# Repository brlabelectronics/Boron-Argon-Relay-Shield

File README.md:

# Boron-Argon-Relay-Shield
Documents and source code for the Boron-Argon Relay Shield.
The Eagle design files can be found in the PCB design files folder.

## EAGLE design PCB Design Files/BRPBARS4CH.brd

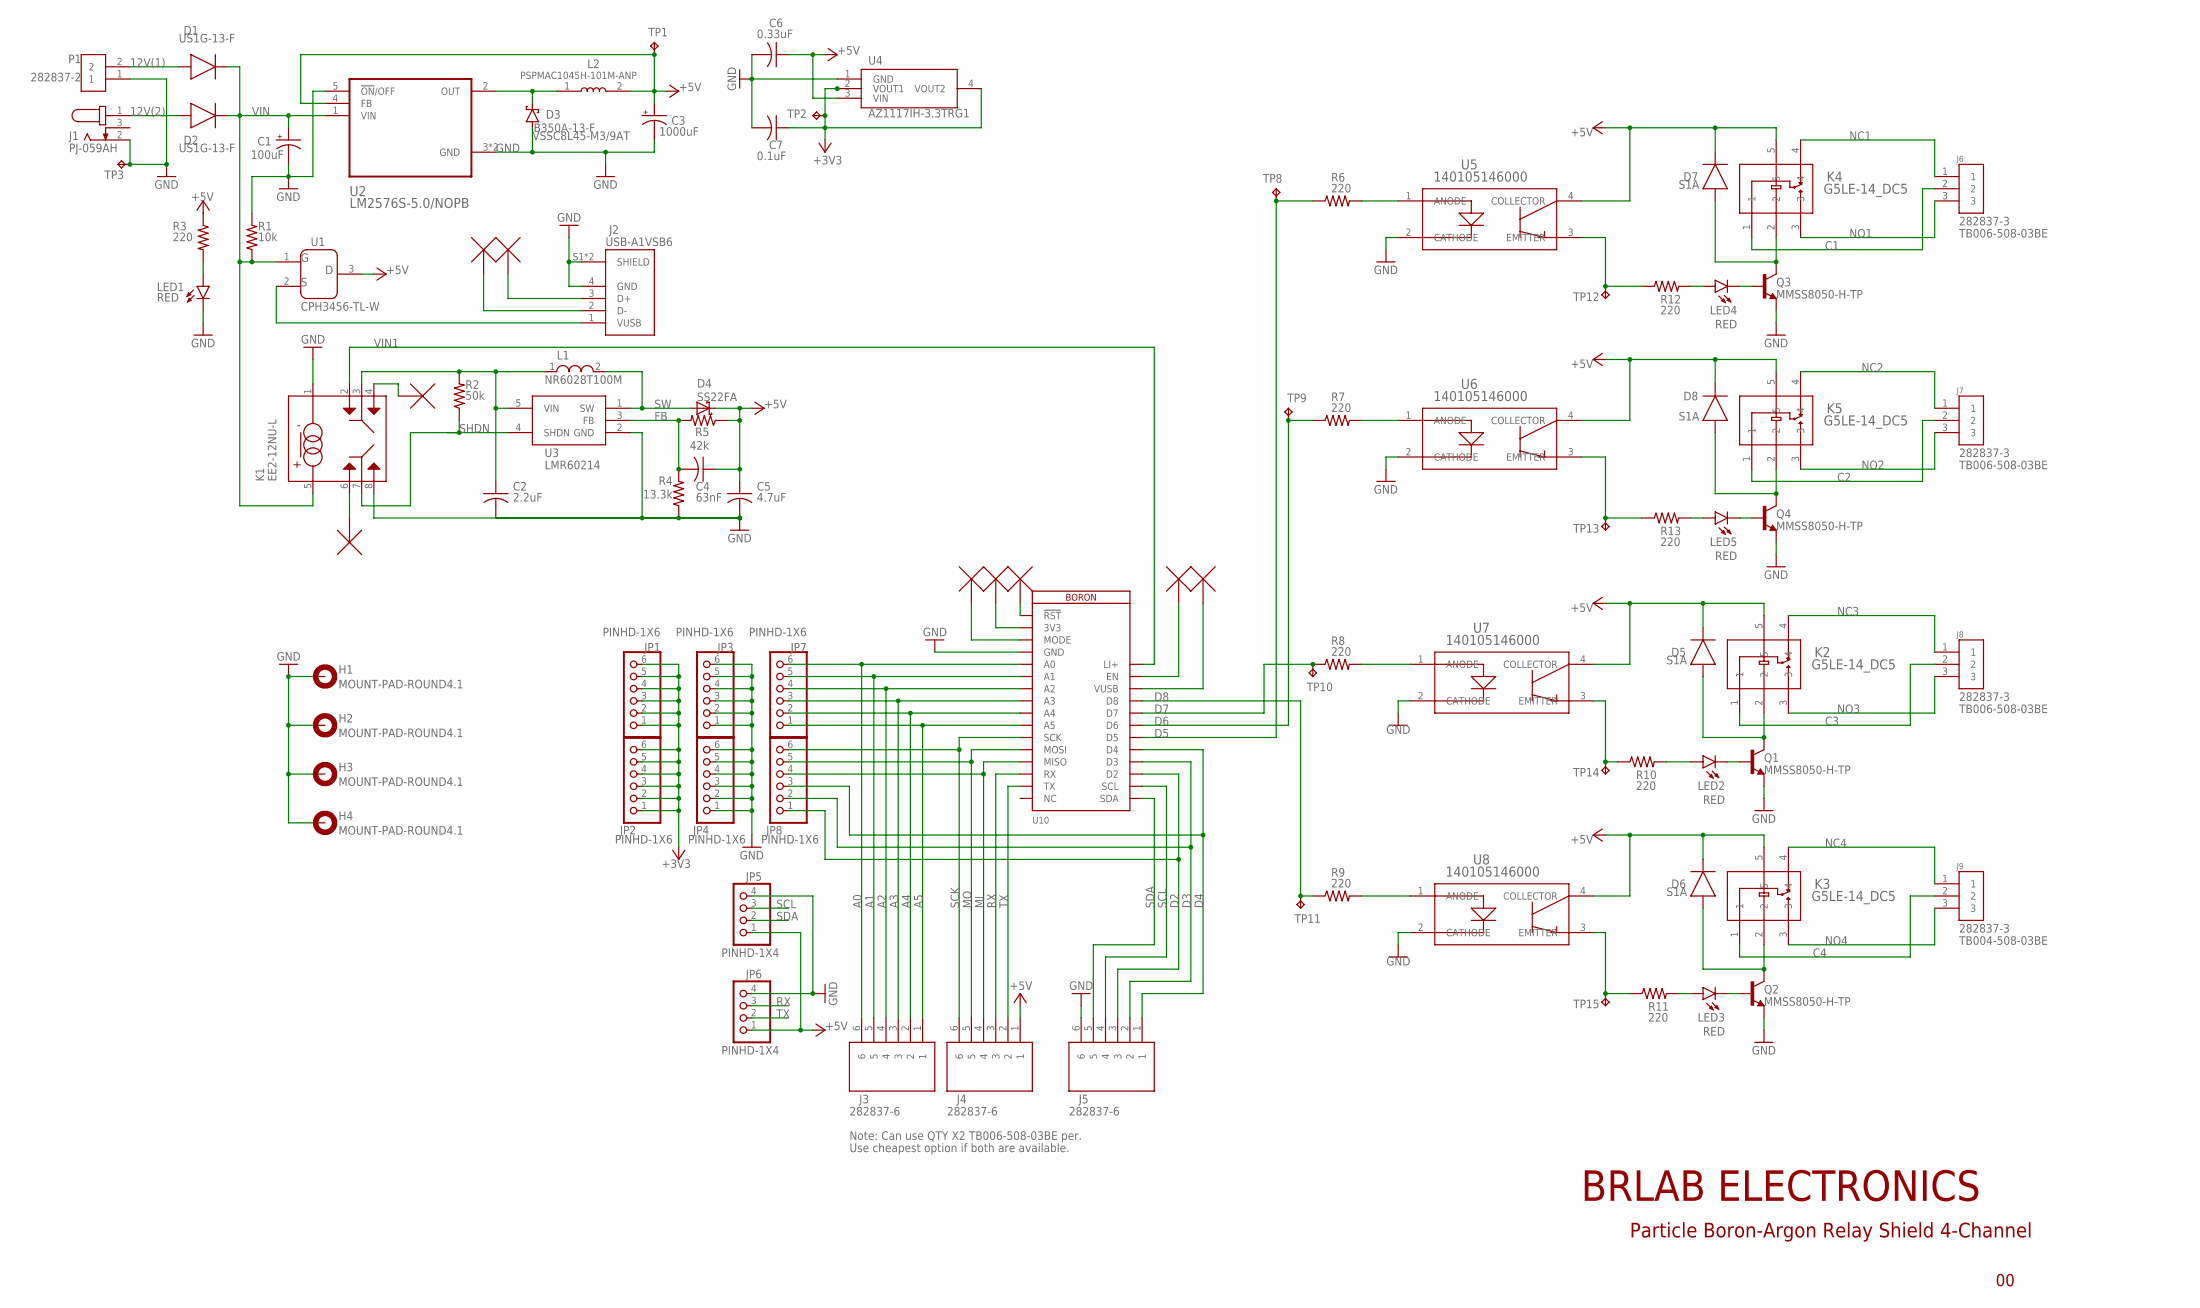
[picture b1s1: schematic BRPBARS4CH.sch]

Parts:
C1: 100uF; 153CLV-0605
C2: 2.2uF; C0805
C3: 1000uF; 153CLV-0810
C4: 63nF; C0805
C5: 4.7uF; C0805
C6: 0.33uF; C1206
C7: 0.1uF; C1206
D1, D2: RS1G-13-F; DIOM5226X290N
D3: B350A-13-F; SMB
D4: SS22FA
D5, D6, D7, D8: DIODE; DIOM5226X290N
H1, H2, H3, H4: MOUNT-PAD-ROUND4.1; 4,1-PAD
J1: PJ-059AH; CUI_PJ-059AH
J2: USB-A1VSB6; ONSHORE_USB-A1VSB6
J3, J4, J5: 282837-6; TE_282837-6
J6, J7, J8, J9: 282837-3; TE_282837-3
JP1, JP2, JP3, JP4, JP7, JP8: PINHD-1X6; 1X06
JP5, JP6: PINHD-1X4; 1X04
K1: EE2-12NU-L
K2, K3, K4, K5: G5LE-14_DC5; RELAY_G5LE-1_DC5_OMR
L1: NR6028T100M
L2: 100uH; PSPMAC1045H-101M-ANP
LED1, LED2, LED3, LED4, LED5: RED; CHIPLED_1206
P1: 282837-2; TE_282837-2
Q1, Q2, Q3, Q4: MMSS8050-H-TP; TRANS_MMSS8050-H-TP
R1: 10k; R1206
R2: 50k; R0805
R3, R6, R7, R8, R9, R10, R11, R12, R13: 220; R1206
R4: 13.3k; R0805
R5: 42k; R0805
TP1, TP2, TP3, TP8, TP9, TP10, TP11, TP12, TP13, TP14, TP15: TPB1,27; B1,27
U1: CPH3456-TL-W
U2: LM2576S-5.0/NOPB; VREG_TPS79625KTTR
U3: LMR60214; SOT95P280X145-5N
U4: AZ1117IH-3.3TRG1; SOT223
U5, U6, U7, U8: 140105146000; SO_5146000_WRE
U10: BORON

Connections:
12V(1): D1.2 (A), P1.2
12V(2): D2.2 (A), J1.1
+3V3: C7.1, JP1.1, JP1.2, JP1.3, JP1.4, JP1.5, JP1.6, JP2.1, JP2.2, JP2.3, JP2.4, JP2.5, JP2.6, TP2.TP, U4.2 (VOUT1), U4.4 (VOUT2)
+5V: C3.+, C4.1, C5.1, C6.1, D4.2 (C), D5.1 (C), D6.1 (C), D7.1 (C), D8.1 (C), J4.1, JP5.1, JP6.1, K2.5, K3.5, K4.5, K5.5, L2.2, R3.1, R5.1, TP1.TP, U1.3, U2.4 (FB), U4.3 (VIN), U5.4 (COLLECTOR), U6.4 (COLLECTOR), U7.4 (COLLECTOR), U8.4 (COLLECTOR)
A0: J3.6, JP7.6, U10.5 (A0)
A1: J3.5, JP7.5, U10.6 (A1)
A2: J3.4, JP7.4, U10.7 (A2)
A3: J3.3, JP7.3, U10.8 (A3)
A4: J3.2, JP7.2, U10.9 (A4)
A5: J3.1, JP7.1, U10.10 (A5)
C1: J6.2, K4.1
C2: J7.2, K5.1
C3: J8.2, K2.1
C4: J9.2, K3.1
D2: J5.3, JP8.1, U10.19 (D2)
D3: J5.2, JP8.2, U10.20 (D3)
D4: J5.1, JP8.3, U10.21 (D4)
D5: R6.1, TP8.TP, U10.22 (D5)
D6: R7.1, TP9.TP, U10.23 (D6)
D7: R8.1, TP10.TP, U10.24 (D7)
D8: R9.1, TP11.TP, U10.25 (D8)
FB: C4.2, R4.2, R5.2, U3.3 (FB)
GND: C1.-, C2.2, C3.-, C5.2, C6.2, C7.2, D3.A, H1.B4,1, H2.B4,1, H3.B4,1, H4.B4,1, J1.2, J2.4 (GND), J2.S1 (SHIELD), J2.S2 (SHIELD), J5.6, JP3.1, JP3.2, JP3.3, JP3.4, JP3.5, JP3.6, JP4.1, JP4.2, JP4.3, JP4.4, JP4.5, JP4.6, JP5.4, JP6.4, K1.1, K1.8, LED1.C, P1.1, Q1.2 (E), Q2.2 (E), Q3.2 (E), Q4.2 (E), R1.2, R4.1, TP3.TP, U2.3 (GND), U2.5 (!ON!/OFF), U2.6 (GND), U3.2 (GND), U4.1 (GND), U5.2 (CATHODE), U6.2 (CATHODE), U7.2 (CATHODE), U8.2 (CATHODE), U10.4 (GND)
MI: J4.4, JP8.4, U10.13 (MISO)
MO: J4.5, JP8.5, U10.12 (MOSI)
unnamed: R12.1, TP12.TP, U5.3 (EMITTER)
unnamed: LED2.A, R10.2
unnamed: D7.2 (A), K4.2, Q3.3 (C)
unnamed: LED4.C, Q3.1 (B)
unnamed: LED5.C, Q4.1 (B)
unnamed: D8.2 (A), K5.2, Q4.3 (C)
unnamed: LED3.A, R11.2
unnamed: LED4.A, R12.2
unnamed: R9.2, U8.1 (ANODE)
unnamed: R8.2, U7.1 (ANODE)
unnamed: C2.1, K1.3, L1.1, R2.2, U3.5 (VIN)
unnamed: LED5.A, R13.2
unnamed: R11.1, TP15.TP, U8.3 (EMITTER)
unnamed: R10.1, TP14.TP, U7.3 (EMITTER)
unnamed: R6.2, U5.1 (ANODE)
unnamed: R13.1, TP13.TP, U6.3 (EMITTER)
unnamed: LED1.A, R3.2
unnamed: J2.1 (VUSB), U1.2
unnamed: D5.2 (A), K2.2, Q1.3 (C)
unnamed: R7.2, U6.1 (ANODE)
unnamed: LED2.C, Q1.1 (B)
unnamed: LED3.C, Q2.1 (B)
unnamed: D6.2 (A), K3.2, Q2.3 (C)
NC1: J6.1, K4.4
NC2: J7.1, K5.4
NC3: J8.1, K2.4
NC4: J9.1, K3.4
NO1: J6.3, K4.3
NO2: J7.3, K5.3
NO3: J8.3, K2.3
NO4: J9.3, K3.3
OUT: D3.C, L2.1, U2.2 (OUT)
RX: J4.3, JP6.3, U10.14 (RX)
SCK: J4.6, JP8.6, U10.11 (SCK)
SCL: J5.4, JP5.3, U10.18 (SCL)
SDA: J5.5, JP5.2, U10.17 (SDA)
SHDN: K1.7, R2.1, U3.4 (SHDN)
SW: D4.1 (A), L1.2, U3.1 (SW)
TX: J4.2, JP6.2, U10.15 (TX)
VIN: C1.+, D1.1 (C), D2.1 (C), K1.5, R1.1, U1.1, U2.1 (VIN)
VIN1: K1.2, U10.28 (LI+)

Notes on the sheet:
VSSC8L45-M3/9AT
S1A
PSPMAC1045H-101M-ANP
TB006-508-03BE
282837-3
TB004-508-03BE
US1G-13-F
Note: Can use QTY X2 TB006-508-03BE per.
Use cheapest option if both are available.
Particle Boron-Argon Relay Shield 4-Channel
BRLAB ELECTRONICS

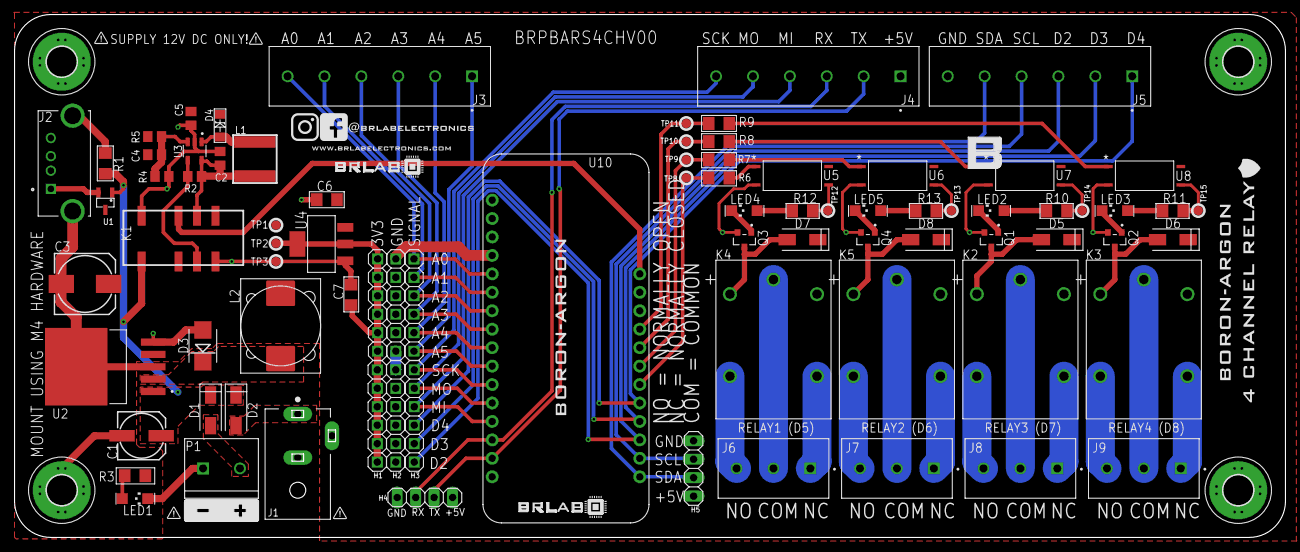
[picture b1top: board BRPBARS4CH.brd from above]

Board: 2 copper layers, 175.0 x 72.0 mm, 86 parts (0 on the bottom side), 66 nets.

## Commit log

2021-11-19 Added source code for controlling relays over wifi on Particle Argon
2021-11-19 -added Blynk library master
2021-11-19 -Added current time and day function and print them to the terminal for debugging purposes
2021-11-19 -All DAYS Scheduler button functionality added (under development)
2021-11-19 -added function to update the ALL DAYS Scheduler on a time interval and ALL DAYS Button state
2021-11-22 Added case structure to alldays
2021-11-22 Changed output messages to user.
2021-11-22 Added WEEKDAYS schedule code
2021-11-22 Changed user messages
2021-11-22 changes users messages and cleaned formatting
2021-11-22 Added code for leading 0 when min is less than 10
2021-11-22 added user message to start up
2021-11-22 added weekend & custom schedule options
2021-11-22 added weekend & custom buttons
2021-11-22 fixed logic for weekend & custom sch time input widget
2021-11-22 added logic so that relay turns off when active time is deselected
2021-11-22 added your own BLYNK TEMPLATE _ID, DEVICE_NAME, and AUTH_TOKEN
2021-11-22 added notes for code and cleaned up formatting
2021-12-09 Added buttons and logic to select which relay would be in automatic mode (schedule mode)
2021-12-09 Fixed BLYNK virtual pin labelling. Added wifi signal strength reading
2021-12-09 Added WiFi Strength to label in terminal screen
2021-12-10 cleaned up code; added wifi strength and battery SoC to Terminal label for user to see
2021-12-10 Added Note About Battery SoC gauge
2021-12-10 added for loop to get average battery voltage for SoC calculation
2022-02-01 -Added PCB design files
2022-02-01 Added PCB design files
2022-02-07 Added Boron-Argon Relay Shield User Manual
2022-02-09 -Renamed to Argon_Relay_Scheduler_Option1
2022-02-09 -Fixed Spelling Error
2022-02-09 -Updated Wifi Strength and Battery SoC placement

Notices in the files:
parts and their libraries:
Particle-Devices: Licensing: Designed by Particle.
COPYRIGHT: Copyright (C) 2018 Accelerated Designs. All rights reserved
COPYRIGHT: Copyright (C) 2021 Ultra Librarian. All rights reserved.
